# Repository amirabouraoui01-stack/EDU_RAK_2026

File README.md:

# VeillePorte

Projet d’Amira : concevoir un dispositif pédagogique qui signale l’état ouvert ou fermé d’une porte dans l’accompagnement de personnes atteintes de la maladie d’Alzheimer. Le capteur infrarouge mesure la distance à une cible fixée sur la porte. Le RAK3172 transmet l’état par LoRaWAN 868 MHz.

Le système ne reconnaît personne, n’identifie pas le sens de passage et ne prouve pas qu’une personne est sortie. Il complète l’information disponible pour le personnel ; il ne remplace pas l’accompagnement humain.

## Fichier de conception retenu

Ouvrir **[le projet KiCad VeillePorte](VeillePorte/veilleporte_complet.kicad_pro)**. Le schéma A2, son PDF, sa netlist et son rapport ERC sont dans le même dossier. Le projet utilise les bibliothèques locales de symboles et d’empreintes.

| Fonction | Composant / raccordement |
|---|---|
| Microcontrôleur et LoRaWAN | RAK3172(H), bande 868 MHz |
| Détection de porte | Module VL53L4CD Pololu 3692, relié par J23 |
| Récupération d’énergie | BQ25570, réglé pour un stockage limité à 4 V |
| Antenne | IFA imprimée 868 MHz, empreinte KiCad liée à RF et masse |
| Interface | UART2, SWD, reset et BOOT0 |

J23 est le brochage du câble du projet, pas l’ordre physique des pastilles du module. Voir le [câblage du capteur](docs/CAPTEUR_IR.md). Les composants NC et C22 de la feuille BQ sont conservés. Le schéma BQ original reste dans l’archive EDU RAK sous references/.

## État actuel

- Schéma : 47 composants ; 0 erreur ERC et 3 avertissements documentés.
- PCB routé : 40 × 60 mm, quatre couches, 1,6 mm ; plan GND sur In2.Cu, 19 vias GND et perçages de vias de 0,3 mm minimum.
- Contrôle PCB et concordance avec le schéma : **0 erreur, 0 avertissement et 0 connexion manquante**.
- [Vues 3D et STEP](VeillePorte/README.md#vues-et-exports) disponibles ; versions précédentes conservées dans [archives](archives/README.md).
- Antenne : géométrie CST conservée, zone 30 × 20 mm. Accord à 868 MHz à revalider sur le PCB de 1,6 mm et dans le boîtier ; le résultat CST historique ne valide pas cette nouvelle carte.
- Firmware, mesures d’autonomie et essais radio sur prototype : à réaliser.

La carte routée de l’ancienne version accéléromètre n’est pas une carte VeillePorte et n’est plus présentée comme version courante. Aucun prototype n’a été validé sur banc.

## Documents du projet final

- [Architecture et limites](docs/ARCHITECTURE.md)
- [Spécification fonctionnelle](docs/VEILLEPORTE.md)
- [Alimentation BQ25570](docs/ALIMENTATION.md)
- [Capteur IR et câble J23](docs/CAPTEUR_IR.md)
- [Antenne CST et intégration](docs/ANTENNE_CST.md)
- [Empreinte KiCad de l’antenne](docs/EMPREINTE_ANTENNE.md)
- [État et validations](docs/ETAT_DU_PROJET.md)
- [Préparation des essais](docs/MISE_EN_SERVICE.md)

## Chaîne fonctionnelle

```mermaid
flowchart LR
  S[Panneau solaire] --> B[BQ25570]
  B <--> C[Supercondensateur, 4 V max]
  B --> R[RAK3172]
  I[VL53L4CD sur le cadre] <-->|I²C, INT, XSHUT| R
  R -->|LoRaWAN 868 MHz| G[Passerelle et serveur]
  G --> T[Tableau de bord du personnel]
```

## Reprendre le projet

1. Cloner https://github.com/amirabouraoui01-stack/EDU_RAK_2026.git.
2. Ouvrir VeillePorte/veilleporte_complet.kicad_pro avec KiCad 10.
3. Consulter le [PDF A2](VeillePorte/veilleporte_complet.pdf) ou le [rapport ERC](VeillePorte/erc_complet.json).
4. Examiner le PCB routé, ses vues 3D et ses rapports ; revalider la radio sur l’empilage réel avant fabrication, puis réaliser les essais sur banc.

L’archive references/EDU_RAK_2026/ conserve les documents pédagogiques d’origine, dont le BQ25570 source. Elle n’est pas une seconde version du projet actif.

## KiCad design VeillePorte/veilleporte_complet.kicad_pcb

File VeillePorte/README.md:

# Projet KiCad retenu — VeillePorte

Ouvrir **veilleporte_complet.kicad_pro**. Le PCB courant est **veilleporte_complet.kicad_pcb** ; les anciennes versions sont conservées dans `../archives/2026-10-28_avant_reprise_40x60.zip`.

La carte mesure **40 × 60 × 1,6 mm**, en quatre couches. L’épaisseur de 1,6 mm reprend le fichier `project_v1.kicad_pcb` de Dorian DIANA. Le radiateur issu de CST est conservé dans une zone de **30 × 20 mm**, soit un quart de la surface de carte. Le FR4 reste présent sous l’antenne ; aucun plan de cuivre ne passe sous sa zone rayonnante.

| Couche | Utilisation actuelle |
|---|---|
| F.Cu | Composants, alimentations, trajet RF et raccords locaux aux vias |
| In1.Cu | Liaisons de signaux, dont celles du RAK3172 |
| In2.Cu | Plan GND, sans piste de signal |
| B.Cu | Composants au dos, autres liaisons et raccords locaux |

Des remplissages GND sur les faces externes rejoignent le plan In2.Cu par les vias de masse. Le PCB comporte **427 segments et 55 vias, dont 19 GND**. Tous les vias sont percés à **0,30 mm minimum**. L’audit de chaque segment figure dans `exports/audit_pistes.csv` ; les courts raccords aux pastilles ou vias sont distingués des segments droits et à 45°.

Les **47 empreintes du schéma** sont présentes. Le capteur reste le module externe VL53L4CD Pololu 3692 raccordé à J23 : le détecteur lui-même ne se trouve pas sur cette carte. Les connecteurs J3/J4/J19/J21/J22/J23 sont placés sur les côtés. J10 fournit deux pastilles traversantes de perçage 1 mm pour souder directement les fils du panneau solaire.

R12, C6 et L1 gardent leurs empreintes **0603**. R12 vaut 0 Ω ; C6/L1 restent non montés pour l’adaptation RF. **C22 est conservé non monté**. La branche de court-circuit de l’IFA touche sa pastille GND ; la géométrie du cuivre est inchangée par rapport au générateur CST. La zone d’exclusion et les contours de l’empreinte sont maintenant orientés avec le radiateur.

## Vérifications

- `pcb_drc.json` : **0 erreur, 0 avertissement, 0 connexion manquante et 0 problème de concordance schéma/PCB**.
- `erc_complet.json` : **0 erreur, 3 avertissements connus**, conservés visibles : symboles BQ25570 et RAK différents des copies de bibliothèque, et label local/global de même nom.
- `exports/verification_pcb.json` : dimensions, vias, couches, DNP et empreintes RF.
- Le fil RF inutile se terminant dans le vide a été supprimé du schéma, sans changer le réseau électrique.

## Vues et exports

- [Vue 3D](exports/vue_3d.png)
- [Dessus](exports/vue_dessus.png) · [Dessous](exports/vue_dessous.png)
- [Assemblage STEP avec cuivre et modèles montés](exports/veilleporte.step)
- [Implantation dessus](implantation.svg) · [Implantation dessous](implantation_dos.svg)
- [Schéma PDF A2](veilleporte_complet.pdf) · [Netlist](veilleporte_complet.net)

**Validation RF restante :** le DRC valide les règles géométriques et les connexions, pas l’accord de l’antenne ni l’impédance de la ligne RF. Le CST historique utilisait une carte 30 × 60 mm de 0,8 mm ; le PCB courant est 40 × 60 mm de 1,6 mm. L’empilage réel, l’accord à 868 MHz, le panneau solaire et le boîtier doivent être repris dans la simulation et contrôlés sur prototype avant fabrication en série. Aucun fichier Gerber n’est présenté comme prêt à fabriquer.

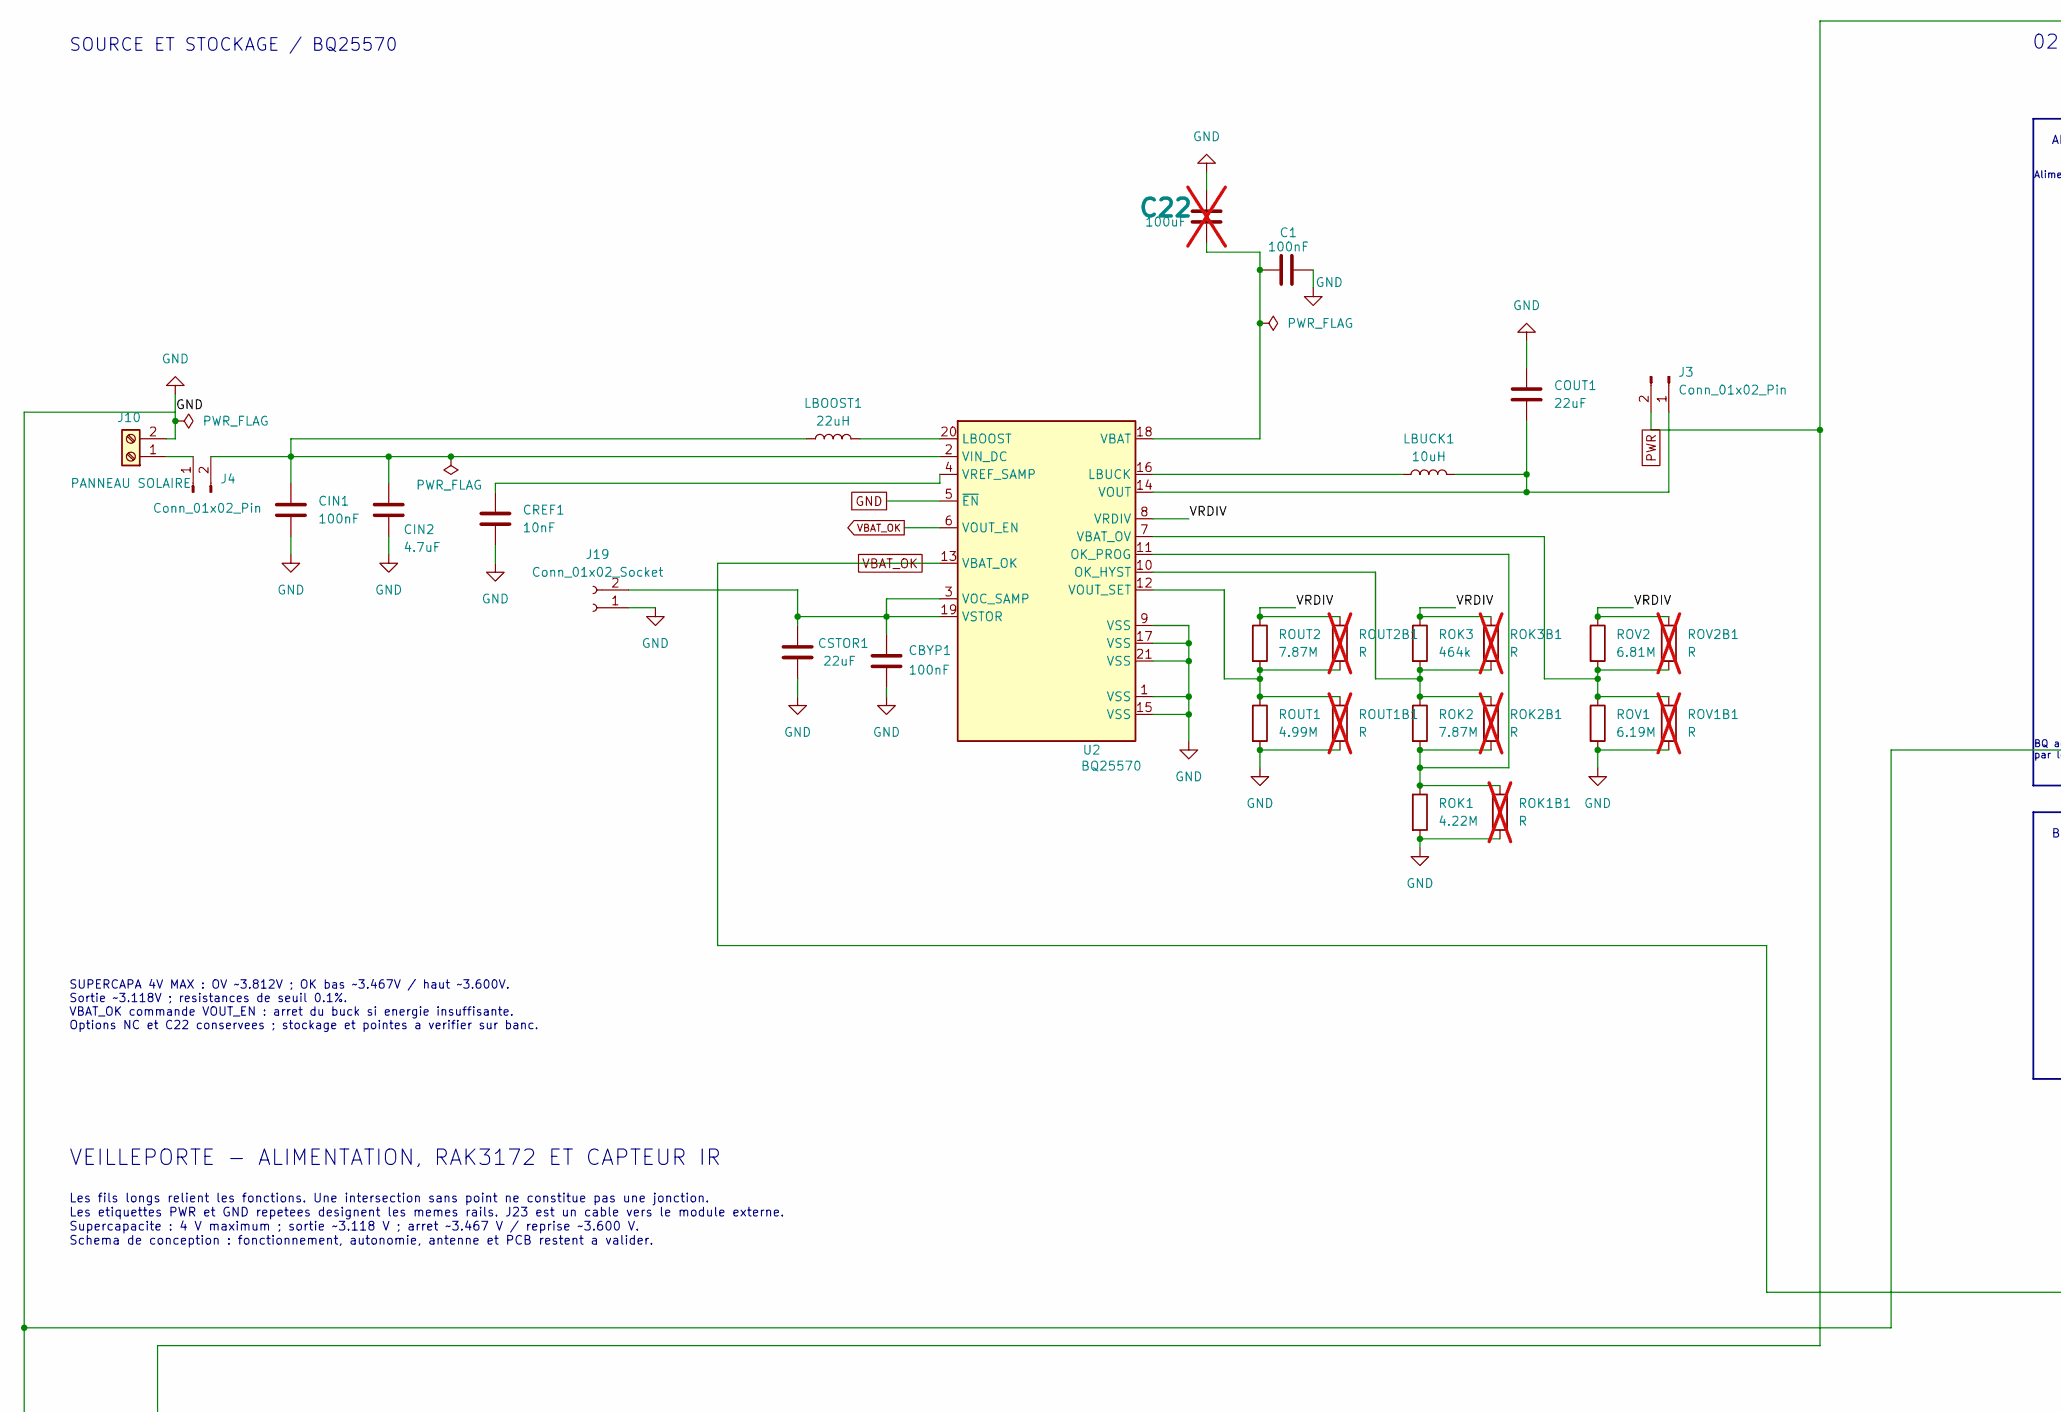
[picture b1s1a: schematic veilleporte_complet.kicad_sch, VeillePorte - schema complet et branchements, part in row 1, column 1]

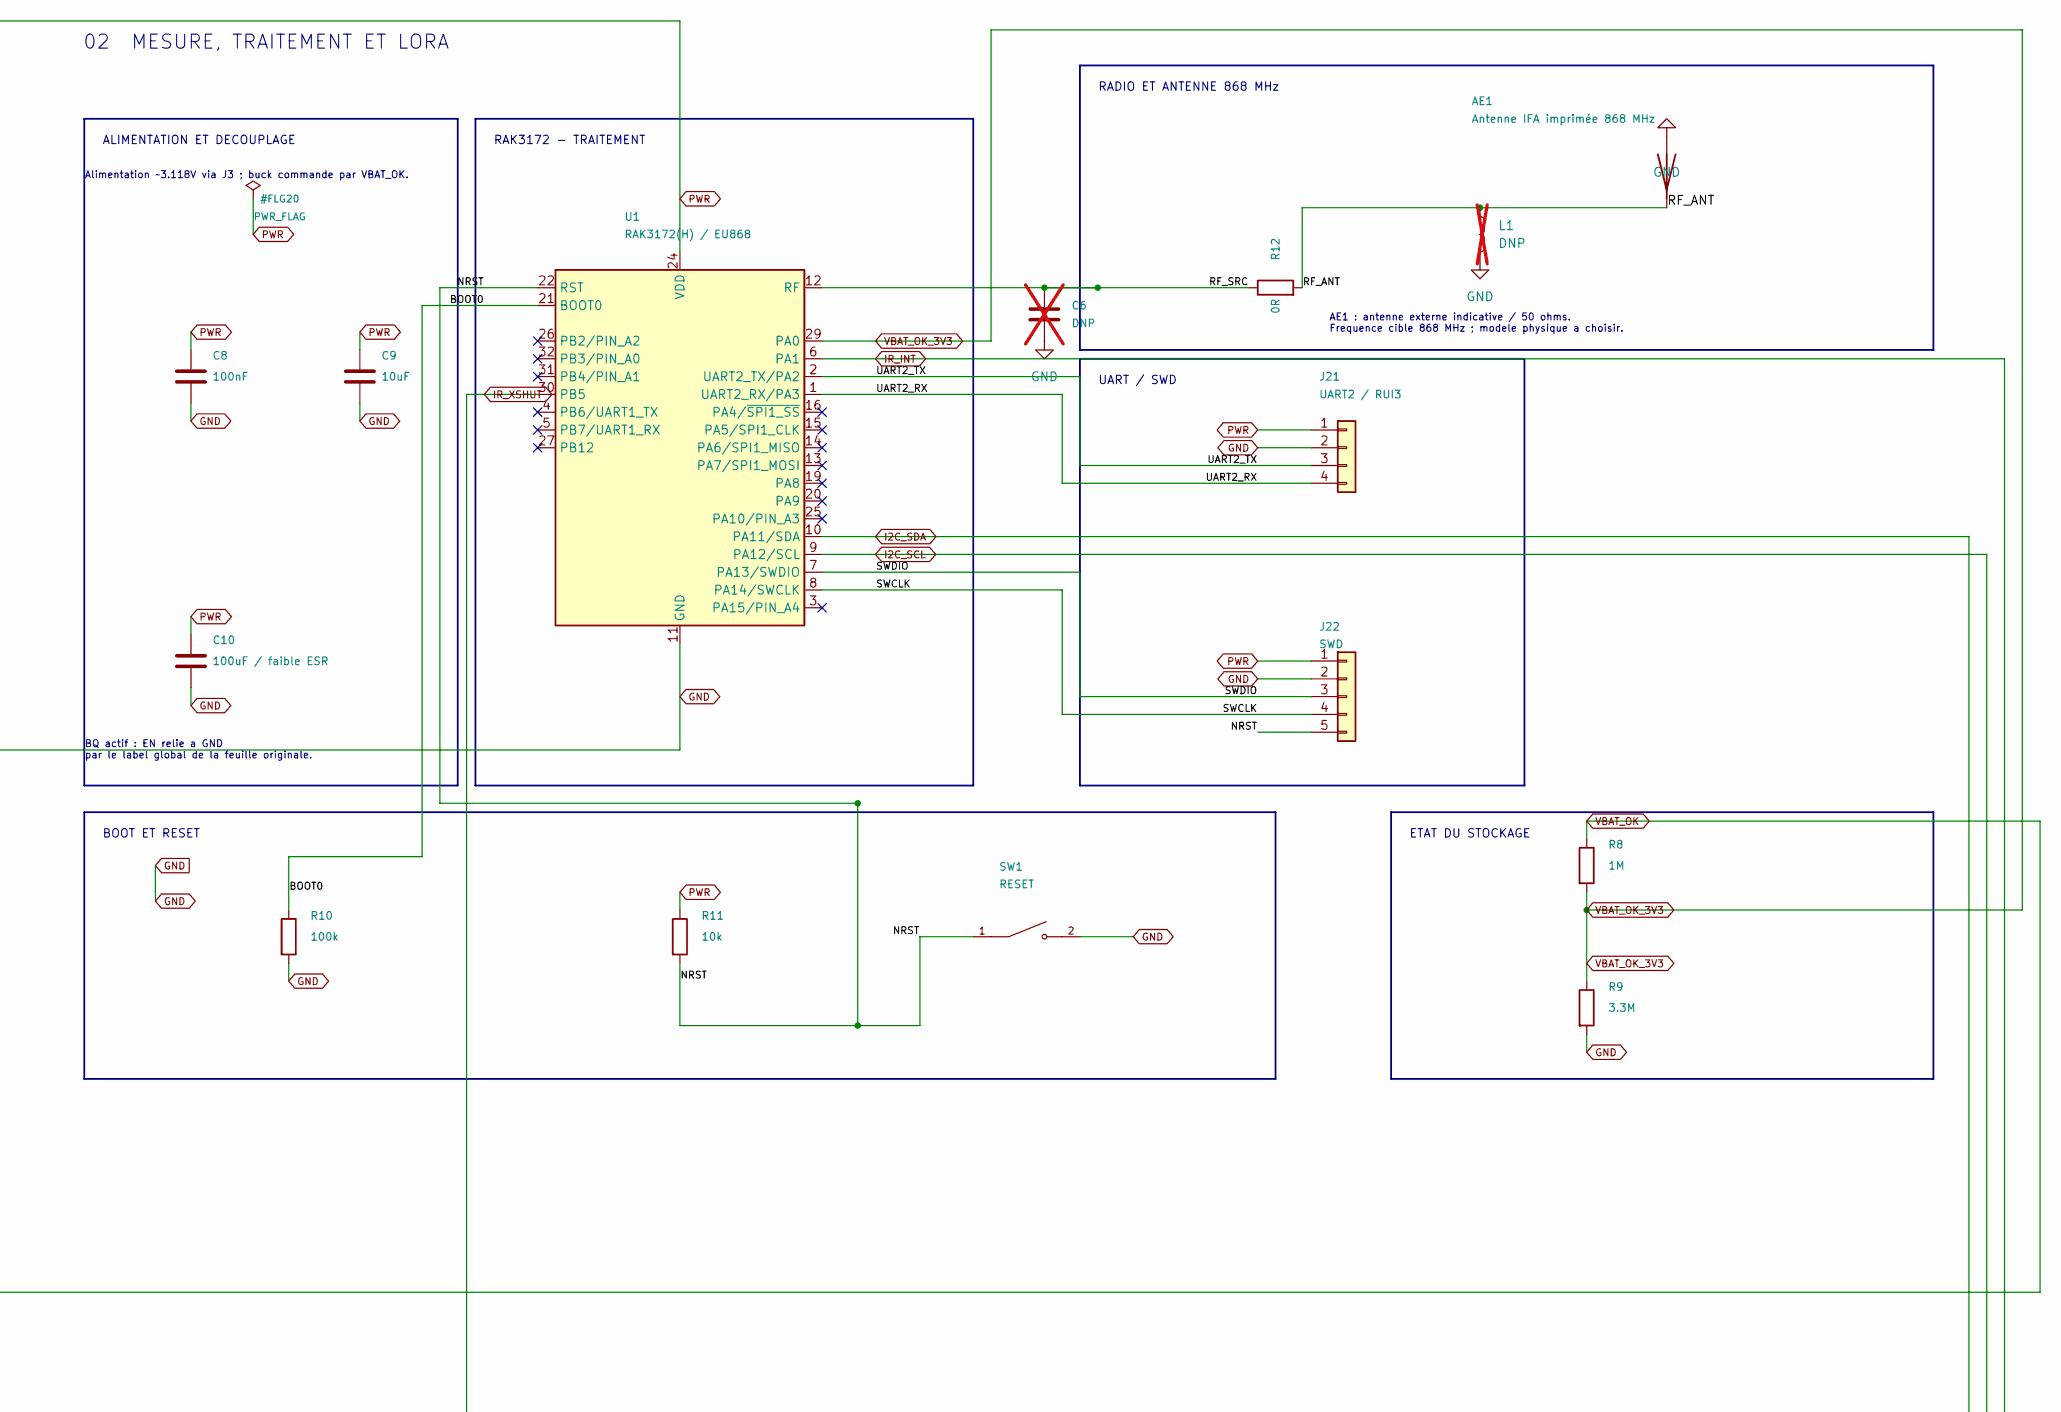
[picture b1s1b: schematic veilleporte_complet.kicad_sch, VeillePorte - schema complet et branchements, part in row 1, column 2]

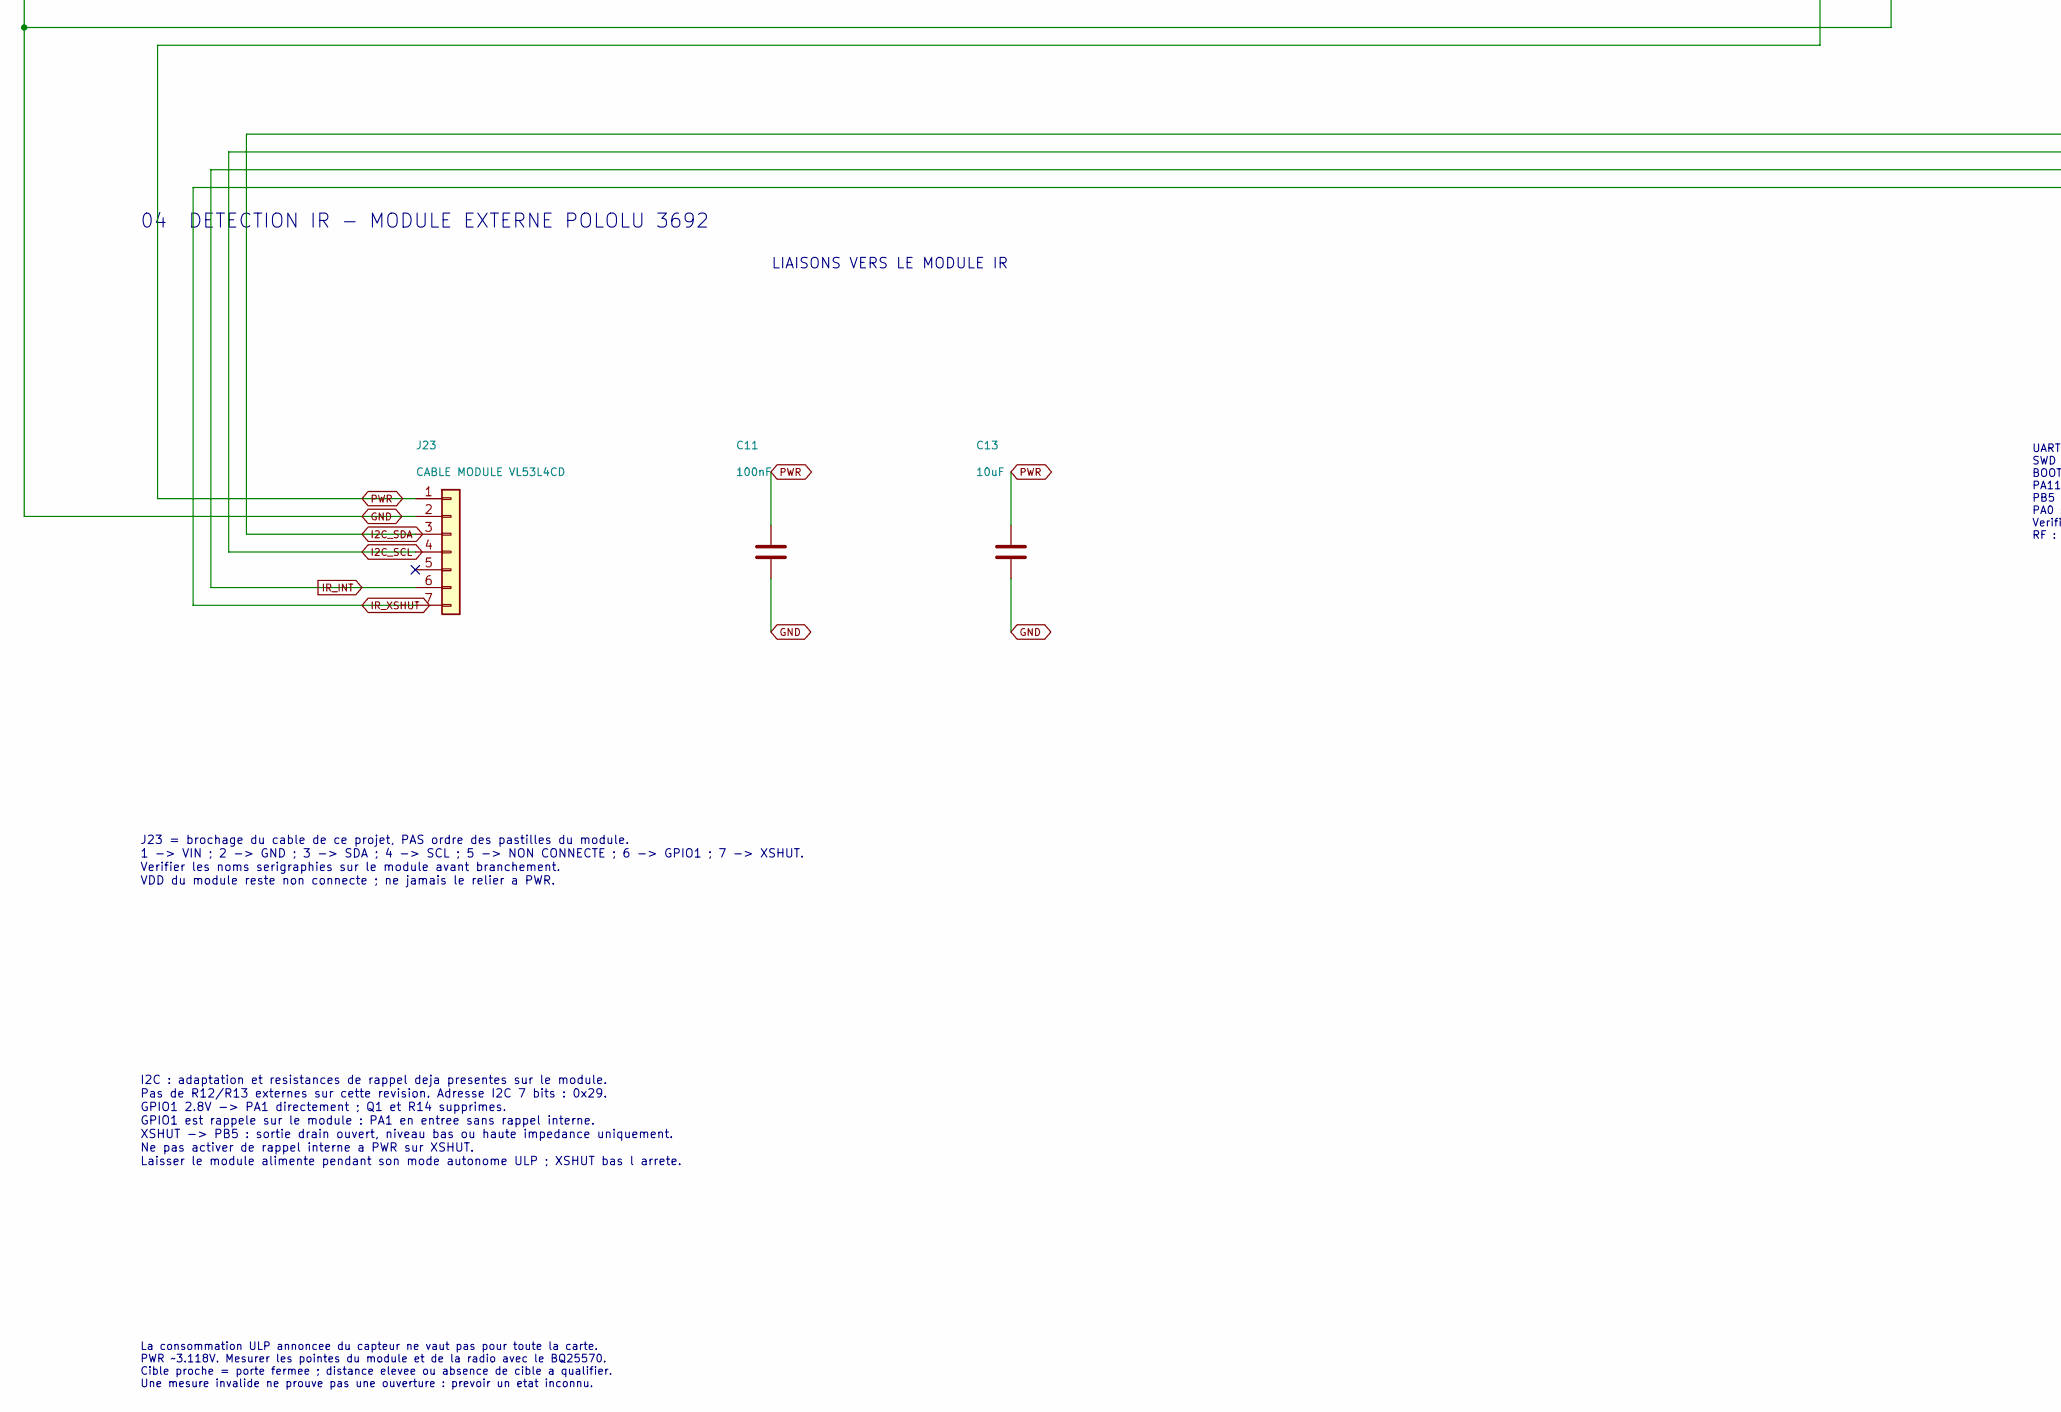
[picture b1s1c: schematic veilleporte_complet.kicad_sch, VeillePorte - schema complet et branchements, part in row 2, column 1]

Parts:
AE1: Antenne IFA imprimée 868 MHz; IFA_868_CST_30x20_PisteFine
C1: 100nF; C_0603_1608Metric; LCSC C1591
C6: DNP; C_0603_1608Metric; not fitted
C8, C11: 100nF; C_0603_1608Metric
C9, C13: 10uF; C_0603_1608Metric
C10: 100uF / faible ESR; C_0805_2012Metric
C22: 100uF; C_0603_1608Metric; not fitted
CBYP1: 100nF; C_0603_1608Metric; LCSC C1591
CIN1: 100nF; C_0603_1608Metric; LCSC C1591
CIN2: 4.7uF; C_0603_1608Metric; LCSC C107368
COUT1: 22uF; C_0603_1608Metric; LCSC C2762594
CREF1: 10nF; C_0603_1608Metric; LCSC C1591
CSTOR1: 22uF; C_0603_1608Metric; LCSC C2762594
J3, J4: Conn_01x02_Pin; PinHeader_1x02_P2.54mm_Vertical; LCSC C3332353
J10: PANNEAU SOLAIRE; Solar_Wires_2x_D1.0_P5.08; LCSC C2683165
J19: Conn_01x02_Socket; PinSocket_1x02_P2.54mm_Vertical; LCSC C5372032
J21: UART2 / RUI3; PinHeader_1x04_P2.54mm_Vertical
J22: SWD; SWD_1x05_P2.54_VeillePorte
J23: CABLE MODULE VL53L4CD; PinHeader_1x07_P2.54mm_Vertical
L1: DNP; L_0603_1608Metric; not fitted
LBOOST1: 22uH; IND_LPS4018-223MRC; LCSC C5441602
LBUCK1: 10uH; L_1008_2520Metric; LCSC C237599
R8: 1M; R_0603_1608Metric
R9: 3.3M; R_0603_1608Metric
R10: 100k; R_0603_1608Metric
R11: 10k; R_0603_1608Metric
R12: 0R; R_0603_1608Metric
ROK1: 4.22M; R_0603_1608Metric; Tolerance 0.1%; LCSC C3009313
ROK1B1, ROK2B1, ROK3B1: R; R_0603_1608Metric; not fitted
ROK2: 7.87M; R_0603_1608Metric; Tolerance 0.1%; LCSC C482913
ROK3: 464k; R_0603_1608Metric; Tolerance 0.1%; LCSC C2930138
ROUT1: 4.99M; R_0603_1608Metric; Tolerance 0.1%; LCSC C2079741
ROUT1B1, ROUT2B1: R; R_0603_1608Metric; not fitted
ROUT2: 7.87M; R_0603_1608Metric; Tolerance 0.1%; LCSC C166757
ROV1: 6.19M; R_0603_1608Metric; Tolerance 0.1%; LCSC C422907
ROV1B1, ROV2B1: R; R_0603_1608Metric; not fitted
ROV2: 6.81M; R_0603_1608Metric; Tolerance 0.1%; LCSC C4087386
SW1: RESET; SW_SPST_B3U-1000P
U1: RAK3172(H) / EU868; RAK3172_VeillePorte
U2: BQ25570; BQ25570_VeillePorte; LCSC C506250

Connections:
/BOOT0: R10.1, U1.21 (BOOT0)
/NRST: J22.5, R11.2, SW1.1, U1.22 (RST)
/RF_ANT: AE1.1 (A), L1.1, R12.2
/RF_SRC: C6.1, R12.1, U1.12 (RF)
/SWCLK: J22.4, U1.8 (PA14/SWCLK)
/SWDIO: J22.3, U1.7 (PA13/SWDIO)
/UART2_RX: J21.4, U1.1 (UART2_RX/PA3)
/UART2_TX: J21.3, U1.2 (UART2_TX/PA2)
/VRDIV: ROK3.1, ROK3B1.1, ROUT2.1, ROUT2B1.1, ROV2.1, ROV2B1.1, U2.8 (VRDIV)
GND: AE1.2 (GND), C1.2, C6.2, C8.2, C9.2, C10.2, C11.2, C13.2, C22.2, CBYP1.2, CIN1.2, CIN2.2, COUT1.1, CREF1.2, CSTOR1.2, J10.2, J19.1, J21.2, J22.2, J23.2, L1.2, R9.2, R10.2, ROK1.2, ROK1B1.2, ROUT1.2, ROUT1B1.2, ROV1.2, ROV1B1.2, SW1.2, U1.11 (GND), U1.17 (GND), U1.18 (GND), U1.23 (GND), U1.28 (GND), U2.1 (VSS), U2.5 (~EN), U2.9 (VSS), U2.15 (VSS), U2.17 (VSS), U2.21 (VSS)
I2C_SCL: J23.4, U1.9 (PA12/SCL)
I2C_SDA: J23.3, U1.10 (PA11/SDA)
IR_INT: J23.6, U1.6 (PA1)
IR_XSHUT: J23.7, U1.30 (PB5)
unnamed: COUT1.2, J3.1, LBUCK1.2, U2.14 (VOUT)
unnamed: CIN1.1, CIN2.1, J4.2, LBOOST1.1, U2.2 (VIN_DC)
unnamed: J4.1, J10.1
unnamed: CBYP1.1, CSTOR1.1, J19.2, U2.3 (VOC_SAMP), U2.19 (VSTOR)
unnamed: LBOOST1.2, U2.20 (LBOOST)
unnamed: LBUCK1.1, U2.16 (LBUCK)
unnamed: ROK2.1, ROK2B1.1, ROK3.2, ROK3B1.2, U2.10 (OK_HYST)
unnamed: ROK1.1, ROK1B1.1, ROK2.2, ROK2B1.2, U2.11 (OK_PROG)
unnamed: C1.1, C22.1, U2.18 (VBAT)
unnamed: ROV1.1, ROV1B1.1, ROV2.2, ROV2B1.2, U2.7 (VBAT_OV)
unnamed: ROUT1.1, ROUT1B1.1, ROUT2.2, ROUT2B1.2, U2.12 (VOUT_SET)
unnamed: CREF1.1, U2.4 (VREF_SAMP)
PWR: C8.1, C9.1, C10.1, C11.1, C13.1, J3.2, J21.1, J22.1, J23.1, R11.1, U1.24 (VDD)
VBAT_OK: R8.1, U2.6 (VOUT_EN), U2.13 (VBAT_OK)
VBAT_OK_3V3: R8.2, R9.1, U1.29 (PA0)

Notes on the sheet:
BQ actif : EN relie a GND par le label global de la feuille originale.
ETAT DU STOCKAGE
Les fils longs relient les fonctions. Une intersection sans point ne constitue pas une jonction. Les etiquettes PWR et GND repetees designent les memes rails. J23 est un cable vers le module externe. Supercapacite : 4 V maximum ; sortie ~3.118 V ; arret ~3.467 V / reprise ~3.600 V. Schema de concep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
UART : adaptateur logique 3.3V ; TX adaptateur vers RX module. SWD : reference tension seulement, eviter deux alimentations simultanees. BOOT0 maintenu bas ; RUI3 se programme par UART2. PA11/PA12 : I2C2 ; PA1 : interruption IR directe 2.8V. PB5 : XSHUT en drain ouvert (bas ou haute impedance). PA0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
SUPERCAPA 4V MAX : OV ~3.812V ; OK bas ~3.467V / haut ~3.600V. Sortie ~3.118V ; resistances de seuil 0.1%. VBAT_OK commande VOUT_EN : arret du buck si energie insuffisante. Options NC et C22 conservees ; stockage et pointes a verifier sur banc.
BOOT ET RESET
AE1 : antenne externe indicative / 50 ohms. Frequence cible 868 MHz ; modele physique a choisir.
Alimentation ~3.118V via J3 ; buck commande par VBAT_OK.
UART / SWD
02 MESURE, TRAITEMENT ET LORA
LIAISONS VERS LE MODULE IR
RAK3172 - TRAITEMENT
ALIMENTATION ET DECOUPLAGE
La consommation ULP annoncee du capteur ne vaut pas pour toute la carte. PWR ~3.118V. Mesurer les pointes du module et de la radio avec le BQ25570. Cible proche = porte fermee ; distance elevee ou absence de cible a qualifier. Une mesure invalide ne prouve pas une ouverture : prevoir un etat inconn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
J23 = brochage du cable de ce projet, PAS ordre des pastilles du module. 1 -> VIN ; 2 -> GND ; 3 -> SDA ; 4 -> SCL ; 5 -> NON CONNECTE ; 6 -> GPIO1 ; 7 -> XSHUT. Verifier les noms serigraphies sur le module avant branchement. VDD du module reste non connecte ; ne jamais le relier a PWR.
I2C : adaptation et resistances de rappel deja presentes sur le module. Pas de R12/R13 externes sur cette revision. Adresse I2C 7 bits : 0x29. GPIO1 2.8V -> PA1 directement ; Q1 et R14 supprimes. GPIO1 est rappele sur le module : PA1 en entree sans rappel interne. XSHUT -> PB5 : sortie drain ouvert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
RADIO ET ANTENNE 868 MHz
SOURCE ET STOCKAGE / BQ25570
VEILLEPORTE - ALIMENTATION, RAK3172 ET CAPTEUR IR
04 DETECTION IR - MODULE EXTERNE POLOLU 3692

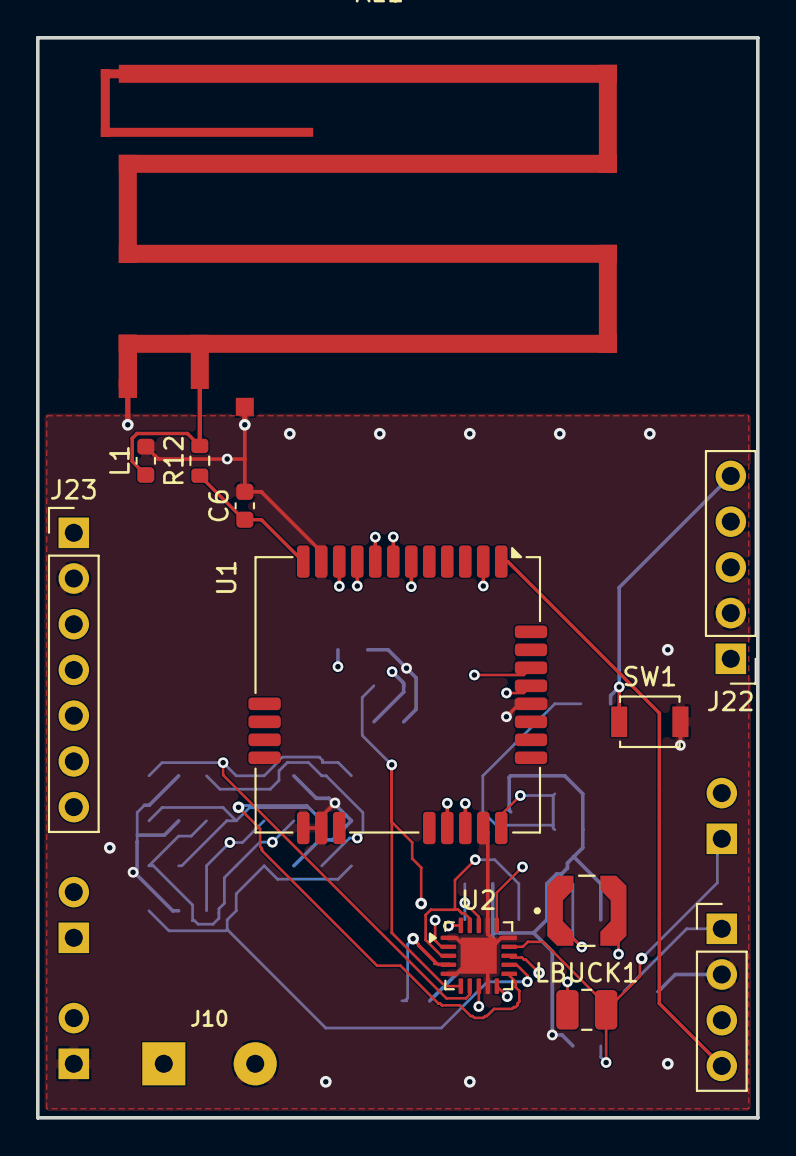
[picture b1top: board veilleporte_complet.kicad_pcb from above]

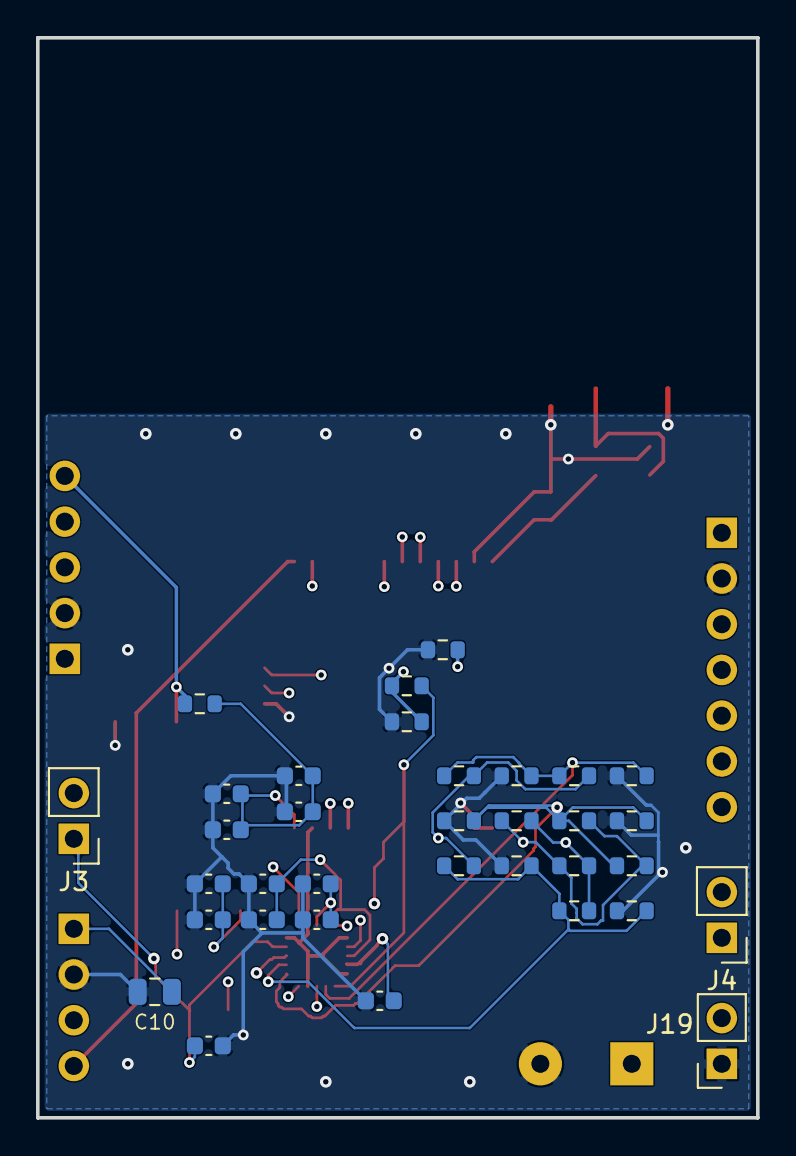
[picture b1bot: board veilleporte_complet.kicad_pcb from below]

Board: 4 copper layers, 40.0 x 60.0 mm, 47 parts (34 on the bottom side), 29 nets.
